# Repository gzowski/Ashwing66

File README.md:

# Ashwing66 Winged Unibody Split Keyboard
66 Key keyboard with both MX and Choc V1 support.

PCB available for purchase via my Etsy page: https://www.etsy.com/uk/listing/1765077057/ashwing66-mechanical-keyboard-pcb

## Features
* 66 Key layout 
* 67 Key for optional rotary encoder or additional key in the center
* Per key LED's for Row 1 and centre cluster keys
* Winged design for ergonomics at 15° angle.
* RP2040 Microcontroller (Pi Pico)
<<<<<<< HEAD
* QMK Firmware with VIA support
* Pre-compiled firmware with VIA and experimental "snap tap" support within Firmware folder.
** "Snap tap" Enable / disable "Lower + Esc" "LED Green On/LED Red Off" 
=======
* QMK Firmware with VIA compatibility
  * QMK: https://config.qmk.fm/#/ashwing66/LAYOUT_5x16
  * VIA: https://usevia.app/
* Pre-compiled firmware with VIA and experimental "snap tap" support within Firmware folder.
  * "Snap tap" Enable / disable "Lower + Esc" "LED Green On/LED Red Off"
>>>>>>> 9c17c4a1c710aafea303e0aeed37a7a769a5664c

## Parts

| Part | Quantity     | Description                | 
| :-------- | :------- | :------------------------- |
| Diodes| 67  | Through-hole 1N4148 or SMD 1N4148W |
| Microcontroller | 1 | Pi Pico RP2040 |
| Switches | 66 or 67 | MX or Choc V1 (67 instead of rotary encoder) |
| EC11 | 0 or 1 | Rotary Encoder for center (depending on configuration) |
| Keycaps | 66 or 67 | 1u switches (depending on configuration) |

## Optional Parts

| Part | Quantity     | Description                |
| :-------- | :------- | :------------------------- |
| LED Diodes | 18 |  SK6812 MINI-E |
| Top Plate | 1 | Lasercut or 3D print options in Plates folder |
| Base Plate | 1 | Lasercut or 3D print options in Plates folder |
| M2 Standoff | 10 | M2x8mm |
| M2 Screws | 10 | M2x6mm | 

## Build Guide

1. Solder PICO micro controller to the top of the PCB facing up (components on top).
  - Next solder the diodes of choice to the back of the PCB, these can be either surface mount or through-hole diodes
    - Take note of diode direction.
    - If using through-hole diodes you'll need to snip the excess from 
the legs on the other side.
2. If you are installing LED's under the 18 switches then you can do this now.
   - The LED's can be dropped into place from the rear of the board. 
   - Ensure that the notch on the GND pin lines up with the triangle marker on the PCB.
   - These can be fiddly to solder and take a bit of patience but once the first leg is soldered then the others become easier. 
3. If you are opting to use a rotary encoder then this can be soldered next.
  - This is positioned in the center and needs to be done before installing a top plate
4. If you are using a top plate read on, otherwise skip to step 5 (To hold switches in place)
   - Place each of your chosen switches into the top plate
     - The pins should be on orintated with the pins north of the the stem if looking straight on.
5. Place the switches down onto the main PCB, ensuring all switches are flush to the board.
   - Turn board over onto the reverse and begin soldering each of the switch pins to the PCB.
6. If you've got a base plate cut then this is where you'll use M2 screws and M2 standoffs to join the top plate to the base.
7. Installing Firmware/Flashing
   - Using QMK from github, building firmware
     - make ashwing66:default:flash or make ashwing66:via:flash (For VIA Support)
   - Copying U2F straight to RP2040 storage
     - Hold down the BOOT button on the Pico while connecting the USB, a new device should be detected as storage.
       - Copy the Ashwing66_via.uf2 file onto the storage.
       - Reconnect the keyboard once the USB storage disappears.

## Default Key Layout

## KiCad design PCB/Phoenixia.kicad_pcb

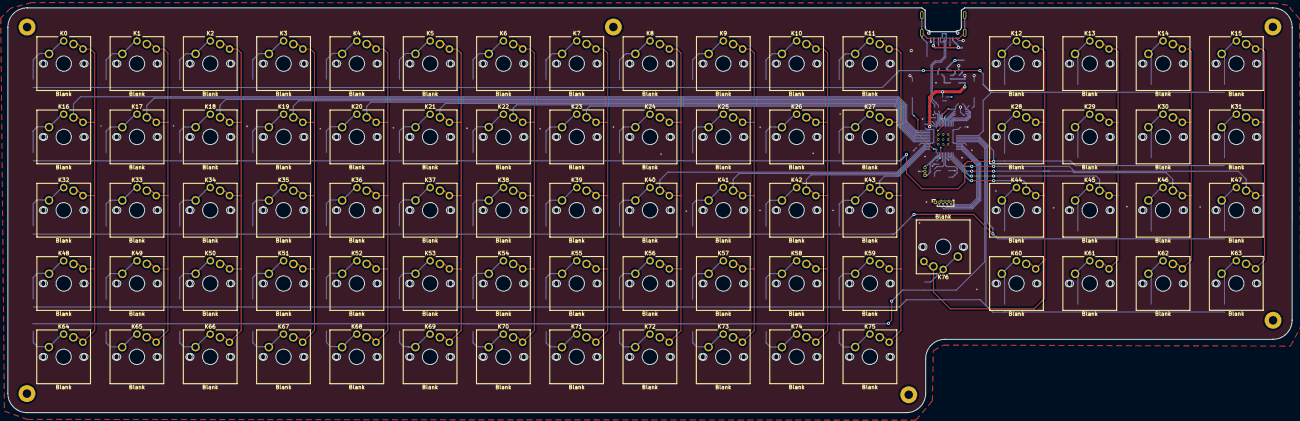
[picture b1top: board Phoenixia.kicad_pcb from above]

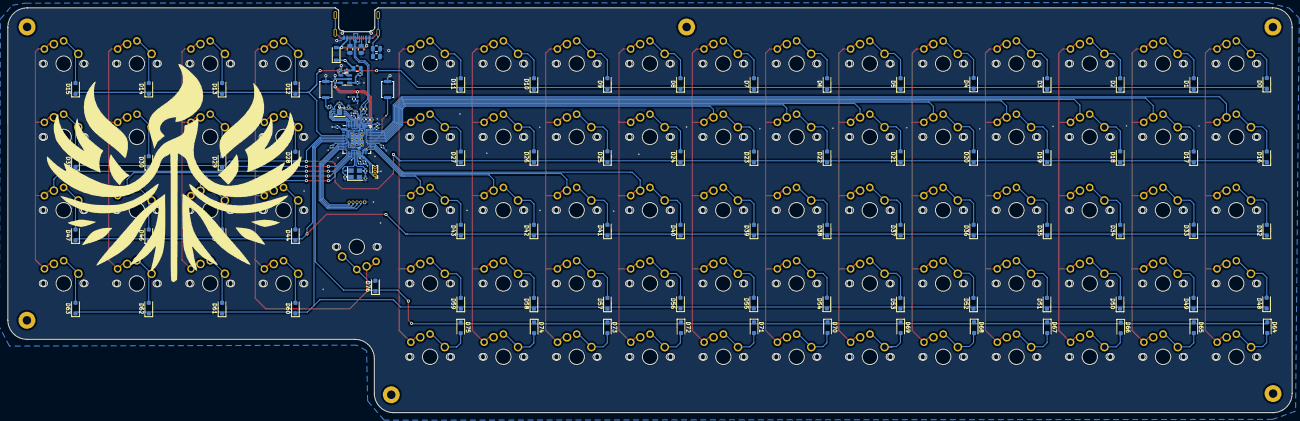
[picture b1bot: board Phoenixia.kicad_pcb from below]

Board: 2 copper layers, 333.8 x 105.2 mm, 201 parts (118 on the bottom side), 127 nets.

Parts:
C1, C4: 10uf 0402; C_0402_1005Metric
C2, C19: 22pf 0402; C_0402_1005Metric
C3: 1uf 0402; C_0402_1005Metric
C5, C6, C7, C8, C11, C13, C14, C15, C16, C18: 100nf 0402; C_0402_1005Metric
C9: 0.1uf; C_0805_2012Metric
C10, C102: 2.2uF 0402; C_0402_1005Metric
CBP1: 10uf 0402; C_0402_1005Metric
D0, D1, D2, D3, D4, D5, D6, D7, D8, D9, D10, D11, D12, D13, D14, D15, D16, D17, D18, D19, D20, D21, D22, D23, D24, D25, D26, D27, D28, D29, D30, D31, D32, D33, D34, D35, D36, D37, D38, D39, D40, D41, D42, D43, D44, D45, D46, D47, D48, D49, D50, D51, D52, D53, D54, D55, D56, D57, D58, D59, D60, D61, D62, D63, D64, D65, D66, D67, D68, D69, D70, D71, D72, D73, D74, D75, D76: D; D_SOD-123F
D100: schottky; D_SOD-123
DLED1: LED; D_0402_1005Metric
F1: 0805L050WR; Fuse_0805_2012Metric
FB1: FerriteBead 0402; R_0402_1005Metric
FLASH1: W25Q16JVUXIQ; SON-8-1EP_3x2mm_P0.5mm_EP1.4x1.6mm
H3, H3#2, H3#3, H3#4, H3#5, H3#6: MountingHole; MountingHole_2.2mm_M2_Pad-Mod
J2: Button; SW_Push_SPST_NO_Alps_SKRK
J5: Conn_01x03_Male; PinHeader_1x03_P1.00mm_Vertical
K0, K1, K2, K3, K4, K5, K6, K7, K8, K9, K10, K11, K12, K13, K14, K15, K16, K17, K18, K19, K20, K21, K22, K23, K24, K25, K26, K27, K28, K29, K30, K31, K32, K33, K34, K35, K36, K37, K38, K39, K40, K41, K42, K43, K44, K45, K46, K47, K48, K49, K50, K51, K52, K53, K54, K55, K56, K57, K58, K59, K60, K61, K62, K63, K64, K65, K66, K67, K68, K69, K70, K71, K72, K73, K74, K75, K76: Blank; SW_Cherry_Choc3_MX_1.00u_PCB
R1, R11: 1K 0402; R_0402_1005Metric
R2: 10K 0402; R_0402_1005Metric
R3, R4: 27r 0402 resistor; R_0402_1005Metric
R5, R6: 5.1K 0402; R_0805_2012Metric
R7: 100K 0402; R_0402_1005Metric
R8: 330r; R_0805_2012Metric
R9: 62ohm 0402; R_0402_1005Metric
RSW1: TSA343G00-250J2; SW_Push_SPST_NO_Alps_SKRK
U1: SOT-23-5 5.5V 3.3V 500mA; SOT-23-5
U3: RP2040; RP2040-QFN-56
USB1: TYPE-C-31-M-14; USB_C_TYPE-C-31-M-14
Y1: 3225_4P 12MHz; Crystal_SMD_3225-4Pin_3.2x2.5mm

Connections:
3V3_EN: R7.1, U1.3 (EN)
+1V1: C3.1, C6.1, C7.1, U3.23 (DVDD), U3.45 (VREG_VOUT), U3.50 (DVDD)
+3V3: C4.1, C5.1, C8.1, C10.1, C11.1, C13.1, C14.1, C15.1, C16.1, C18.1, C102.1, DLED1.2 (A), FLASH1.8 (VCC), R2.1, U1.5 (OUT), U3.1 (IOVDD), U3.10 (IOVDD), U3.22 (IOVDD), U3.33 (IOVDD), U3.42 (IOVDD), U3.43 (ADC_AVDD), U3.44 (VREG_IN), U3.48 (USB_VDD), U3.49 (IOVDD)
/QSPI_SCLK: FLASH1.6 (CLK), U3.52 (QSPI_SCLK)
/QSPI_SD0: FLASH1.5 (DI(IO0)), U3.53 (QSPI_SD0)
/QSPI_SD1: FLASH1.2 (DO(IO1)), U3.55 (QSPI_SD1)
/QSPI_SD2: FLASH1.3 (IO2), U3.54 (QSPI_SD2)
/QSPI_SD3: FLASH1.7 (IO3), U3.51 (QSPI_SD3)
/QSPI_SS: FLASH1.1 (~CS), R1.1, R2.2, U3.56 (QSPI_SS)
/RUN: RSW1.2, U3.26 (RUN)
/SWCLK: J5.1, U3.24 (SWCLK)
/SWD: J5.3, U3.25 (SWD)
/~USB_BOOT: J2.1, R1.2
Col_0: K0.1, K16.1, K32.1, K48.1, K64.1, U3.41 (GPIO29_ADC3)
Col_1: K1.1, K17.1, K33.1, K49.1, K65.1, U3.40 (GPIO28_ADC2)
Col_2: K2.1, K18.1, K34.1, K50.1, K66.1, U3.39 (GPIO27_ADC1)
Col_3: K3.1, K19.1, K35.1, K51.1, K67.1, U3.38 (GPIO26_ADC0)
Col_4: K4.1, K20.1, K36.1, K52.1, K68.1, U3.37 (GPIO25)
Col_5: K5.1, K21.1, K37.1, K53.1, K69.1, U3.36 (GPIO24)
Col_6: K6.1, K22.1, K38.1, K54.1, K70.1, U3.35 (GPIO23)
Col_7: K7.1, K23.1, K39.1, K55.1, K71.1, U3.34 (GPIO22)
Col_8: K8.1, K24.1, K40.1, K56.1, K72.1, U3.32 (GPIO21)
Col_9: K9.1, K25.1, K41.1, K57.1, K73.1, U3.31 (GPIO20)
Col_10: K10.1, K26.1, K42.1, K58.1, K74.1, U3.30 (GPIO19)
Col_11: K11.1, K27.1, K43.1, K59.1, K75.1, U3.29 (GPIO18)
Col_12: K12.1, K28.1, K44.1, K60.1, K76.1, U3.18 (GPIO15)
Col_13: K13.1, K29.1, K45.1, K61.1, U3.17 (GPIO14)
Col_14: K14.1, K30.1, K46.1, K62.1, U3.16 (GPIO13)
Col_15: K15.1, K31.1, K47.1, K63.1, U3.15 (GPIO12)
GND: C1.2, C2.1, C3.2, C4.2, C5.2, C6.2, C7.2, C8.2, C9.2, C10.2, C11.2, C13.2, C14.2, C15.2, C16.2, C18.2, C19.1, C102.2, CBP1.2, FLASH1.4 (GND), FLASH1.9 (EP), J2.2, J5.2, R5.1, R6.1, R8.2, RSW1.1, U1.2 (GND), U3.19 (TESTEN), U3.57 (GND), USB1.A1 (GND), USB1.A12 (GND), USB1.B1 (GND), USB1.B12 (GND), Y1.2, Y1.4
unnamed: C19.2, R11.2, Y1.3
unnamed: D0.2 (A), K0.2
unnamed: D1.2 (A), K1.2
unnamed: D2.2 (A), K2.2
unnamed: D3.2 (A), K3.2
unnamed: D4.2 (A), K4.2
unnamed: D5.2 (A), K5.2
unnamed: D6.2 (A), K6.2
unnamed: D7.2 (A), K7.2
unnamed: D8.2 (A), K8.2
unnamed: D9.2 (A), K9.2
unnamed: D10.2 (A), K10.2
unnamed: D11.2 (A), K11.2
unnamed: D12.2 (A), K12.2
unnamed: D13.2 (A), K13.2
unnamed: D14.2 (A), K14.2
unnamed: D15.2 (A), K15.2
unnamed: D16.2 (A), K16.2
unnamed: D17.2 (A), K17.2
unnamed: D18.2 (A), K18.2
unnamed: D19.2 (A), K19.2
unnamed: D20.2 (A), K20.2
unnamed: D21.2 (A), K21.2
unnamed: D22.2 (A), K22.2
unnamed: D23.2 (A), K23.2
unnamed: D24.2 (A), K24.2
unnamed: D25.2 (A), K25.2
unnamed: D26.2 (A), K26.2
unnamed: D27.2 (A), K27.2
unnamed: D28.2 (A), K28.2
unnamed: D29.2 (A), K29.2
unnamed: D30.2 (A), K30.2
unnamed: D31.2 (A), K31.2
unnamed: D32.2 (A), K32.2
unnamed: D33.2 (A), K33.2
unnamed: D34.2 (A), K34.2
unnamed: D35.2 (A), K35.2
unnamed: D36.2 (A), K36.2
unnamed: D37.2 (A), K37.2
unnamed: D38.2 (A), K38.2
unnamed: D39.2 (A), K39.2
unnamed: D40.2 (A), K40.2
unnamed: D41.2 (A), K41.2
unnamed: D42.2 (A), K42.2
unnamed: D43.2 (A), K43.2
unnamed: D44.2 (A), K44.2
unnamed: D45.2 (A), K45.2
unnamed: D46.2 (A), K46.2
unnamed: D47.2 (A), K47.2
unnamed: D48.2 (A), K48.2
unnamed: D49.2 (A), K49.2
unnamed: D50.2 (A), K50.2
unnamed: D51.2 (A), K51.2
unnamed: D52.2 (A), K52.2
unnamed: D53.2 (A), K53.2
unnamed: D54.2 (A), K54.2
unnamed: D55.2 (A), K55.2
unnamed: D56.2 (A), K56.2
unnamed: D57.2 (A), K57.2
unnamed: D58.2 (A), K58.2
unnamed: D59.2 (A), K59.2
unnamed: D60.2 (A), K60.2
unnamed: D61.2 (A), K61.2
unnamed: D62.2 (A), K62.2
unnamed: D63.2 (A), K63.2
unnamed: D64.2 (A), K64.2
unnamed: D65.2 (A), K65.2
unnamed: D66.2 (A), K66.2
unnamed: D67.2 (A), K67.2
unnamed: D68.2 (A), K68.2
unnamed: D69.2 (A), K69.2
unnamed: D70.2 (A), K70.2
unnamed: D71.2 (A), K71.2
unnamed: D72.2 (A), K72.2
unnamed: D73.2 (A), K73.2
unnamed: D74.2 (A), K74.2
unnamed: D75.2 (A), K75.2
unnamed: D76.2 (A), K76.2
unnamed: F1.1, FB1.1
unnamed: CBP1.1, U1.4 (BP)
unnamed: C1.1, FB1.2, U1.1 (IN)
unnamed: R4.2, U3.46 (USB_DM)
unnamed: R3.2, U3.47 (USB_DP)
unnamed: R5.2, USB1.A5 (CC1)
unnamed: R6.2, USB1.B5 (CC2)
unnamed: C9.1, R8.1, USB1.S1 (SHIELD)
Row_0: D0.1 (K), D1.1 (K), D2.1 (K), D3.1 (K), D4.1 (K), D5.1 (K), D6.1 (K), D7.1 (K), D8.1 (K), D9.1 (K), D10.1 (K), D11.1 (K), D12.1 (K), D13.1 (K), D14.1 (K), D15.1 (K), U3.5 (GPIO3)
Row_1: D16.1 (K), D17.1 (K), D18.1 (K), D19.1 (K), D20.1 (K), D21.1 (K), D22.1 (K), D23.1 (K), D24.1 (K), D25.1 (K), D26.1 (K), D27.1 (K), D28.1 (K), D29.1 (K), D30.1 (K), D31.1 (K), U3.6 (GPIO4)
Row_2: D32.1 (K), D33.1 (K), D34.1 (K), D35.1 (K), D36.1 (K), D37.1 (K), D38.1 (K), D39.1 (K), D40.1 (K), D41.1 (K), D42.1 (K), D43.1 (K), D44.1 (K), D45.1 (K), D46.1 (K), D47.1 (K), U3.7 (GPIO5)
Row_3: D48.1 (K), D49.1 (K), D50.1 (K), D51.1 (K), D52.1 (K), D53.1 (K), D54.1 (K), D55.1 (K), D56.1 (K), D57.1 (K), D58.1 (K), D59.1 (K), D60.1 (K), D61.1 (K), D62.1 (K), D63.1 (K), U3.8 (GPIO6)
Row_4: D64.1 (K), D65.1 (K), D66.1 (K), D67.1 (K), D68.1 (K), D69.1 (K), D70.1 (K), D71.1 (K), D72.1 (K), D73.1 (K), D74.1 (K), D75.1 (K), D76.1 (K), U3.9 (GPIO7)
USB_D+: R3.1, USB1.A6 (D+), USB1.B6 (D+)
USB_D-: R4.1, USB1.A7 (D-), USB1.B7 (D-)
VBUS: D100.2 (A), USB1.A4 (VBUS), USB1.A9 (VBUS), USB1.B4 (VBUS), USB1.B9 (VBUS)
VSYS: D100.1 (K), F1.2, R7.2
XIN: C2.2, U3.20 (XIN), Y1.1
XOUT: R11.1, U3.21 (XOUT)

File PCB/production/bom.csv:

Designator,Footprint,Quantity,Value,LCSC Part #
"C1, C4, CBP1",402,3,10uf 0402, 
"C10, C102",402,2,2.2uF 0402, 
"C11, C13, C14, C15, C16, C18, C5, C6, C7, C8",402,10,100nf 0402, 
"C19, C2",402,2,22pf 0402, 
C3,402,1,1uf 0402, 
C9,805,1,0.1uf,
D100,D_SOD-123,1,1N5817W, 
DLED1,402,1,LED,
F1,805,1,0805L050WR,
FB1,402,1,MFBM1V1005-000-R,
FLASH1,SON-8-1EP_3x2mm_P0.5mm_EP1.4x1.6mm,1,W25Q16JVUXIQ,
J2,SW_Push_SPST_NO_Alps_SKRK,1,Button, 
"R1, R11",402,2,1K 0402, 
R2,402,1,10K 0402,  
"R3, R4",402,2,27r 0402 resistor, 
"R5, R6",805,2,5.1K 0402, 
R7,402,1,100K 0402, 
R8,805,1,330r,
R9,402,1,62ohm 0402, 
RSW1,SW_Push_SPST_NO_Alps_SKRK,1,TSA343G00-250J2,
U1,SOT-23-5,1,SOT-23-5 5.5V 3.3V 500mA, 
U3,RP2040-QFN-56,1,RP2040, C2040
USB1,USB_C_TYPE-C-31-M-14,1,TYPE-C-31-M-14,C319148
Y1,Crystal_SMD_3225-4Pin_3.2x2.5mm,1,3225_4P 12MHz,

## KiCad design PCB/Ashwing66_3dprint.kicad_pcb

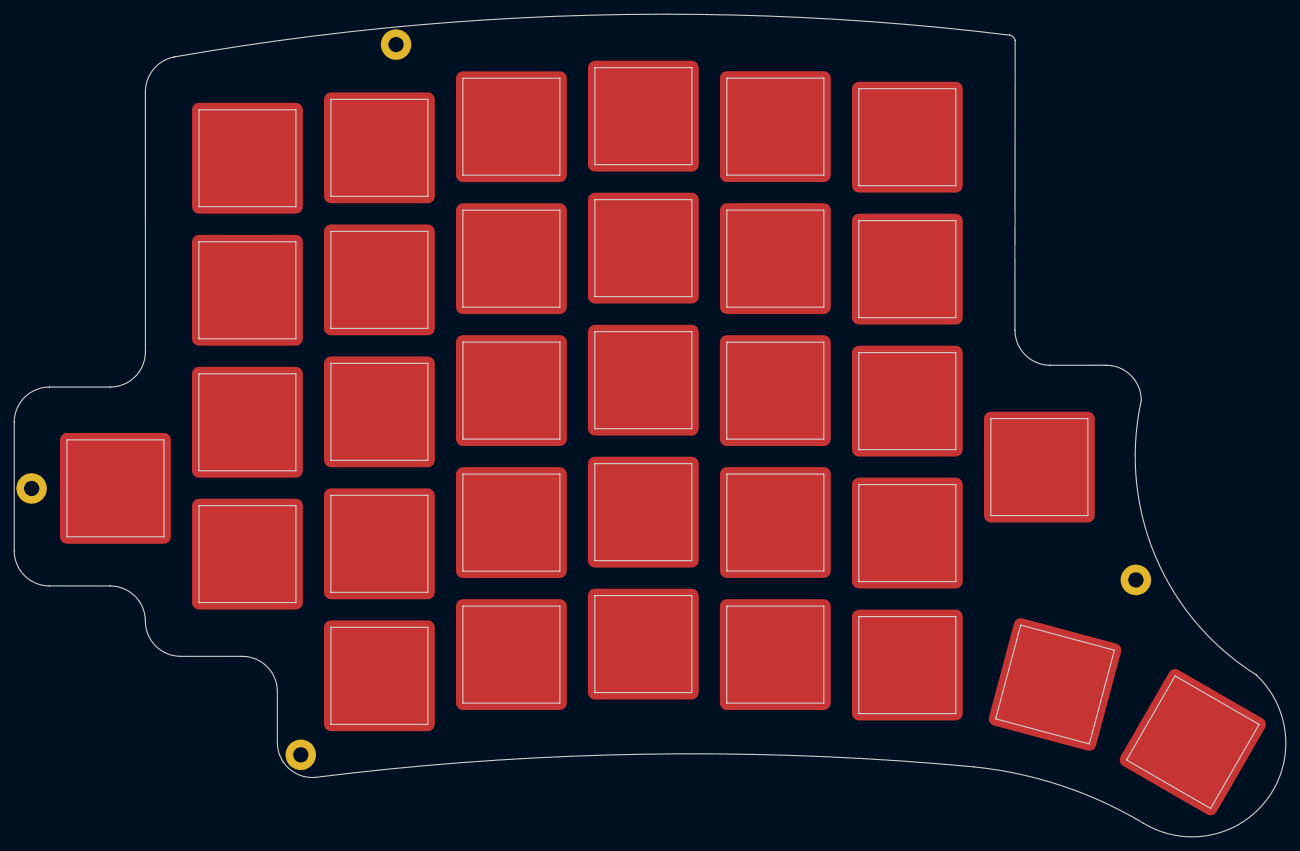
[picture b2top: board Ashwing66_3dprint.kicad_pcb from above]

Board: 2 copper layers, 183.6 x 118.8 mm, 36 parts (0 on the bottom side), 7 nets, no tracks yet.

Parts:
H4, H4#2, H4#3: MountingHole; MountingHole_2.2mm_M2_Pad
K0, K1, K2, K3, K4, K5, K16, K17, K18, K19, K20, K21, K32, K33, K34, K35, K36, K37, K48, K49, K50, K51, K52, K53, K60, K60#2, K64, K65, K66, K67, K68, K69, K69#2: Blank; SW_Cherry_Choc5_MX_1.00u_PCB_LED_3D2_CUTOUT4

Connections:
Col_0: K0.1, K16.1, K32.1, K48.1, K60#2.1
Col_1: K1.1, K17.1, K33.1, K49.1, K64.1
Col_2: K2.1, K18.1, K34.1, K50.1, K65.1
Col_3: K3.1, K19.1, K35.1, K51.1, K66.1
Col_4: K4.1, K20.1, K36.1, K52.1, K67.1
Col_5: K5.1, K21.1, K37.1, K53.1, K68.1
Col_6: K60.1, K69#2.1

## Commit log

2024-05-13 Create Files
2024-05-13 Initial Push
2024-05-15 Fixed Files
2024-05-16 Trace changes and teardrops
2024-05-21 Curved Revision
2024-05-23 Split
2024-05-24 Shape
2024-05-25 NewLayouts
2024-05-25 Addition of Ashwing66
2024-06-02 Sun Jun 2 02:56:42 AM BST 2024
2024-06-03 Change of DIODE
2024-06-08 new layout, added RGB
2024-06-10 Mon Jun 10 03:52:55 PM BST 2024-Final
2024-06-13 Release
2024-07-01 Cleanup
2024-07-01 Added firmware/plates/readme/images
2024-07-06 Update, removed files
2024-07-30 Updates + Snap Tap compiled Firmware
2025-05-14 Additional Plate Files
2025-09-04 Support for ColorHoster added
2025-09-15 Work being carried out on v2
